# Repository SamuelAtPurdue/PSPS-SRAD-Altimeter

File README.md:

# psps_srad_altimeter
<div>
  <h2>Description</h2>
  <br>
  <p>
    PSPS SRAD Altimeter is the backup flight computer for Purdue Space Program Solids 2018/2019. It records altitude, pressure tempurature, and status information to help diagnose problems with opperation and control the recovery system. The altimeter uses breakout boards from Adafruit and Sparkfun and a custom PCB. 
  </p>
</div>

<div>
  <h2>Hardware</h2>
  <br>
  <p>
    This Project uses a custom PCB which is included as eagle files. Hardware list for assembling the PCB can be found in the documentation. The other hardware required are listed below:
    <ul>
      <li> <a href = "https://www.adafruit.com/product/2651">Adafruit BMP280 Breakout</a></li>
      <li> <a href = "https://www.adafruit.com/product/254">Adafruit micro SD Card Breakout</a></li>
      <li> <a href = "https://www.adafruit.com/product/1897">Adafruit SPI FRAM Breakout</a></li>
      <li> <a href = "https://www.sparkfun.com/products/10255">Sparkfun Lipower Boost Converter</a></li>
      <li> <a href = "https://www.sparkfun.com/products/13777">Sparkfun Battery Babysitter</a></li>
    </ul>
  </p>
</div>

<div>
  <h2>Libraries</h2>
  <p>
    This Projects requires some modifications to Adafruit's BMP280 Libraries and the SD Library to work properly. These modified libraries as well as the other ones used are included. Links to the original Libraries below:
    <ul>
      <li> <a href ="https://github.com/adafruit/Adafruit_BMP280_Library">Adafruit BMP280</a></li>
      <li> <a href = "https://github.com/adafruit/SD">SD</a></li>
      <li> <a href = "https://github.com/adafruit/Adafruit_FRAM_SPI">Adafruit SPI FRAM</a></li>
      <li> <a href = "https://github.com/adafruit/Adafruit_Sensor">Adafruit Sensor</a></li>
      <li> <a href = "https://github.com/sparkfun/SparkFun_BQ27441_Arduino_Library">Battery Babysitter</a></li>
    </ul>
  </p>
</div>

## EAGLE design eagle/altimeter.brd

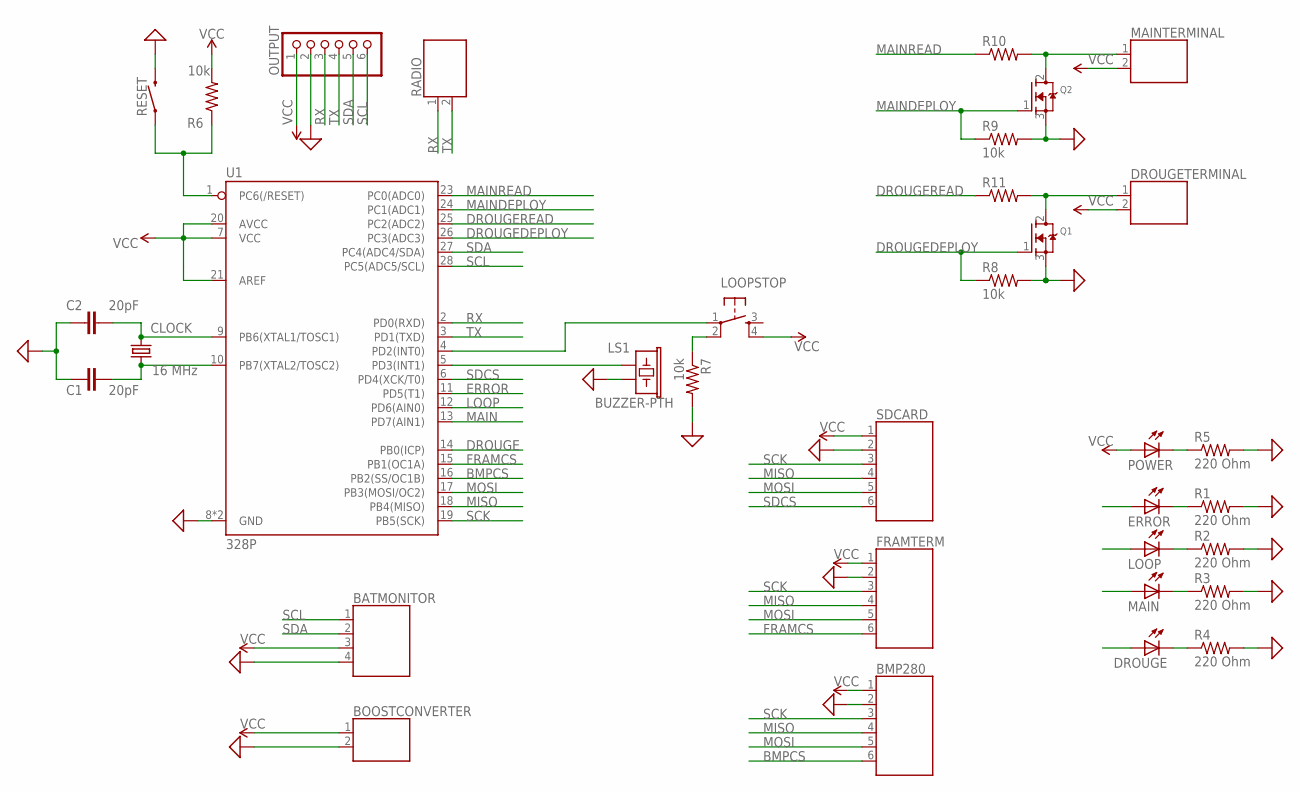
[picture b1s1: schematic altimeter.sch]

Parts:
BATMONITOR: 691386700004
BMP280: 691386700006
BOOSTCONVERTER: 691386700002
C1, C2: 20pF; CAP-PTH-2.54
CLOCK: 16 MHz; HC49U-V
DROUGE: LED5MM
DROUGETERMINAL: 691386700002
ERROR: LED5MM
FRAMTERM: 691386700006
LOOP: LED5MM
LOOPSTOP: TAC_SWITCHPTH; TACTILE-PTH
LS1: BUZZER-PTH; BUZZER-12MM
MAIN: LED5MM
MAINTERMINAL: 691386700002
OUTPUT: PINHD-1X6; 1X06
POWER: LED5MM
Q1, Q2: MOSFET-NGDS_TO220V; TO220V
R1, R2, R3, R4, R5: 220 Ohm; 0204/7
R6, R7, R8, R9: 10k; 0204/7
R10, R11: R-US_0204/7; 0204/7
RADIO: 691386700002
RESET: MOMENTARY-SWITCH-SPST-PTH-6.0MM; TACTILE_SWITCH_PTH_6.0MM
SDCARD: 691386700006
U1: 328P; DIP28

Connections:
BMPCS: BMP280.6, U1.16 (PB2(SS/OC1B))
DROUGE: DROUGE.A, U1.14 (PB0(ICP))
DROUGEDEPLOY: Q1.1 (G), R8.1, U1.26 (PC3(ADC3))
DROUGEREAD: R11.1, U1.25 (PC2(ADC2))
ERROR: ERROR.A, U1.11 (PD5(T1))
FRAMCS: FRAMTERM.6, U1.15 (PB1(OC1A))
GND: BATMONITOR.4, BMP280.2, BOOSTCONVERTER.2, C1.1, C2.1, FRAMTERM.2, LS1.- (2), OUTPUT.2, Q1.3 (S), Q2.3 (S), R1.2, R2.2, R3.2, R4.2, R5.2, R7.2, R8.2, R9.2, RESET.3 (2), SDCARD.2, U1.8 (GND), U1.22 (GND)
LOOP: LOOP.A, U1.12 (PD6(AIN0))
MAIN: MAIN.A, U1.13 (PD7(AIN1))
MAINDEPLOY: Q2.1 (G), R9.1, U1.24 (PC1(ADC1))
MAINREAD: R10.1, U1.23 (PC0(ADC0))
MISO: BMP280.4, FRAMTERM.4, SDCARD.4, U1.18 (PB4(MISO))
MOSI: BMP280.5, FRAMTERM.5, SDCARD.5, U1.17 (PB3(MOSI/OC2))
unnamed: C1.2, CLOCK.1, U1.10 (PB7(XTAL2/TOSC2))
unnamed: C2.2, CLOCK.2, U1.9 (PB6(XTAL1/TOSC1))
unnamed: POWER.K (C), R5.1
unnamed: LOOPSTOP.2, R7.1
unnamed: LOOPSTOP.1, U1.4 (PD2(INT0))
unnamed: LS1.+ (1), U1.5 (PD3(INT1))
unnamed: DROUGETERMINAL.1, Q1.2 (D), R11.2
unnamed: MAINTERMINAL.1, Q2.2 (D), R10.2
unnamed: ERROR.K (C), R1.1
unnamed: LOOP.K (C), R2.1
unnamed: MAIN.K (C), R3.1
unnamed: DROUGE.K (C), R4.1
unnamed: R6.1, RESET.1, U1.1 (PC6(/RESET))
RX: OUTPUT.3, RADIO.1, U1.2 (PD0(RXD))
SCK: BMP280.3, FRAMTERM.3, SDCARD.3, U1.19 (PB5(SCK))
SCL: BATMONITOR.1, OUTPUT.6, U1.28 (PC5(ADC5/SCL))
SDA: BATMONITOR.2, OUTPUT.5, U1.27 (PC4(ADC4/SDA))
SDCS: SDCARD.6, U1.6 (PD4(XCK/T0))
TX: OUTPUT.4, RADIO.2, U1.3 (PD1(TXD))
VCC: BATMONITOR.3, BMP280.1, BOOSTCONVERTER.1, DROUGETERMINAL.2, FRAMTERM.1, LOOPSTOP.4, MAINTERMINAL.2, OUTPUT.1, POWER.A, R6.2, SDCARD.1, U1.7 (VCC), U1.20 (AVCC), U1.21 (AREF)

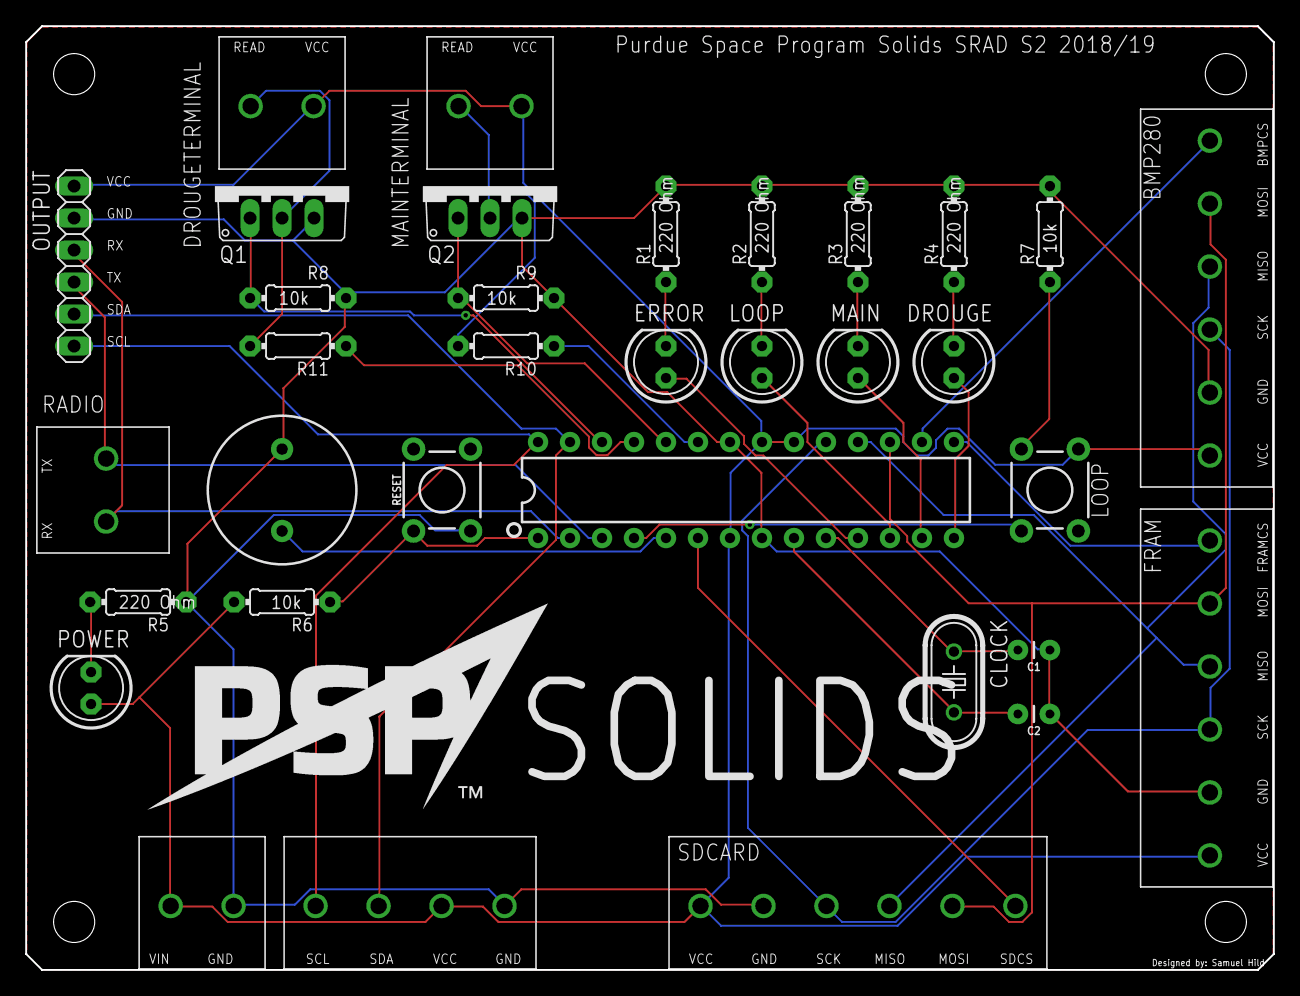
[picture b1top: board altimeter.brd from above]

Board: 2 copper layers, 99.1 x 74.9 mm, 34 parts (0 on the bottom side), 33 nets.

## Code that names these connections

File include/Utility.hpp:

#include <Arduino.h>
/*
 * header:      Utility.hpp
 * description: provides utility functions to be used by other classes
 * author:      Samuel Hild
 */

// Pinout Values
#define SDCS 4
#define FRAMCS 9
#define BMPCS 10
#define MAIN_DEPLOY A1
#define MAIN_READ A0
#define DROGUE_DEPLOY A3
#define DROGUE_READ A2
#define BUZZER 3
#define LOOP_STOP 2
#define ERROR_LED 5
#define LOOP_LED 6
#define MAIN_LED 7
#define DROGUE_LED 8
#define RADIO_INTERFACE_RX 0
#define RADIO_INTERFACE_TX 1

// Refresh rates and Delays
#define REFRESH_RATE 5
#define STARTUP_DELAY 15
#define STARTUP_CONST 1
#define DEPLOY_DELAY 500
#define BURN_SAMPLE_RATE 5
#define ASCENT_SAMPLE_RATE 0.25

// Sensor Settings
#define BATTERY_CAPACITY 500
#define PACKET_SIZE 104
#define ERRANT_PRESSUE -1
#define FRAM_SIZE 8192

// Threshold Values
#define LAUNCH_ALTITUDE_THRESHOLD 100
#define LAUNCH_VELOCITY_THRESHOLD 10
#define LAUNCH_ACCELERATION_THRESHOLD 50

#define BURN_TIME_THRESHOLD 15
#define APOGEE_VELOCITY_THRESHOLD 5
#define MAIN_ALTITUDE_THRESHOLD 1000
#define ZERO_THRESHOLD 0

// Debug
#define RADIO_ENABLE 0

/*
 * enum:        Runmode
 * description: provides the runmode for performing specified actions and flight checks
 * author:      Samuel Hild
 */
enum Runmode {PREFLIGHT, BURN, ASCENT, APOGEE, DROGUE, MAIN, POSTFLIGHT};

/*
 * struct:      collectedData
 * description: provides a data structure for the data collected each loop
 * author:      Samuel Hild
 */
struct collectedData 
{
  // collection info  
  uint32_t timestamp;
  uint32_t number;

  // Sensor Data
  float altitude;
  float pressure;
  float tempurature;

  // Derived Data
  float velocity;
  float acceleration;

  // System Information
  uint16_t ram;
  uint16_t mainVoltage;
  uint16_t drogueVoltage;

  // Power System Information
  float lipoVoltage;
  float lipoCurrent;
  float lipoCapacity;
};

void fatal (const __FlashStringHelper *);
void error (const __FlashStringHelper *);
void alert (const __FlashStringHelper *);
void debug (const __FlashStringHelper *);

void blink(int);

int freeRam();

void dataCopy(collectedData *, collectedData *);

void clearEEPROM();

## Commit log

2019-02-28 Added Eagle Files
2019-02-28 Rename altimeter_new.brd to altimeter.brd
2019-02-28 Rename altimeter_new.sch to altimeter.sch
2019-03-29 Created project structure and updated eagle files
2019-03-30 Created interfaces
2019-03-30 fixed interfaces
2019-04-01 Updated Project
2019-04-02 Added functionality
2019-04-08 Added more functionality
2019-05-14 Updated Central Structure
2019-05-17 Finshed Primary Features
2019-05-17 Finished Primary Function
2019-05-17 Add .vscode to git ignore
2019-05-17 Created Initial Readme
2019-06-17 Made Radio Changes
2019-06-18 Added Tempurature Transmission to Radio
2019-06-18 updated data checking code

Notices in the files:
parts and their libraries:
Wurth_Elektronik_Electromechanic_Termina: Copyright: Würth Elektronik
SparkFun-Capacitors: Licensing: Creative Commons ShareAlike 4.0 International - https://creativecommons.org/licenses/by-sa/4.0
